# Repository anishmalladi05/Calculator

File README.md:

# Calculator
16 key calculator with a 128 by 32 pixel display and low profile choc switches. Uses circuit python. I made it to challenge myself and use a screen in my builds. I also wanted to try choc switches without building a whole keyboard.

## Assembly:
Look at the assembly video in the repo
<br></br>
Step 1:
<br></br>
Solder PCB components on
<br></br>
Step 2:
<br></br>
Assemble it into case according to the video

## Flashing:
To flash, press BOOT on the board, and while pressing boot, press reset, then release reset, and THEN release boot
<br></br>
Upload the UF2 File into the drive called RP1-RP2
<br></br>
Open the drive called CIRCUITPY
<br></br>
Delete everything in there
<br></br>
Replace it with everything in the folder called code so it looks like this:
<br></br>

<br></br>
Enjoy!

## Images:

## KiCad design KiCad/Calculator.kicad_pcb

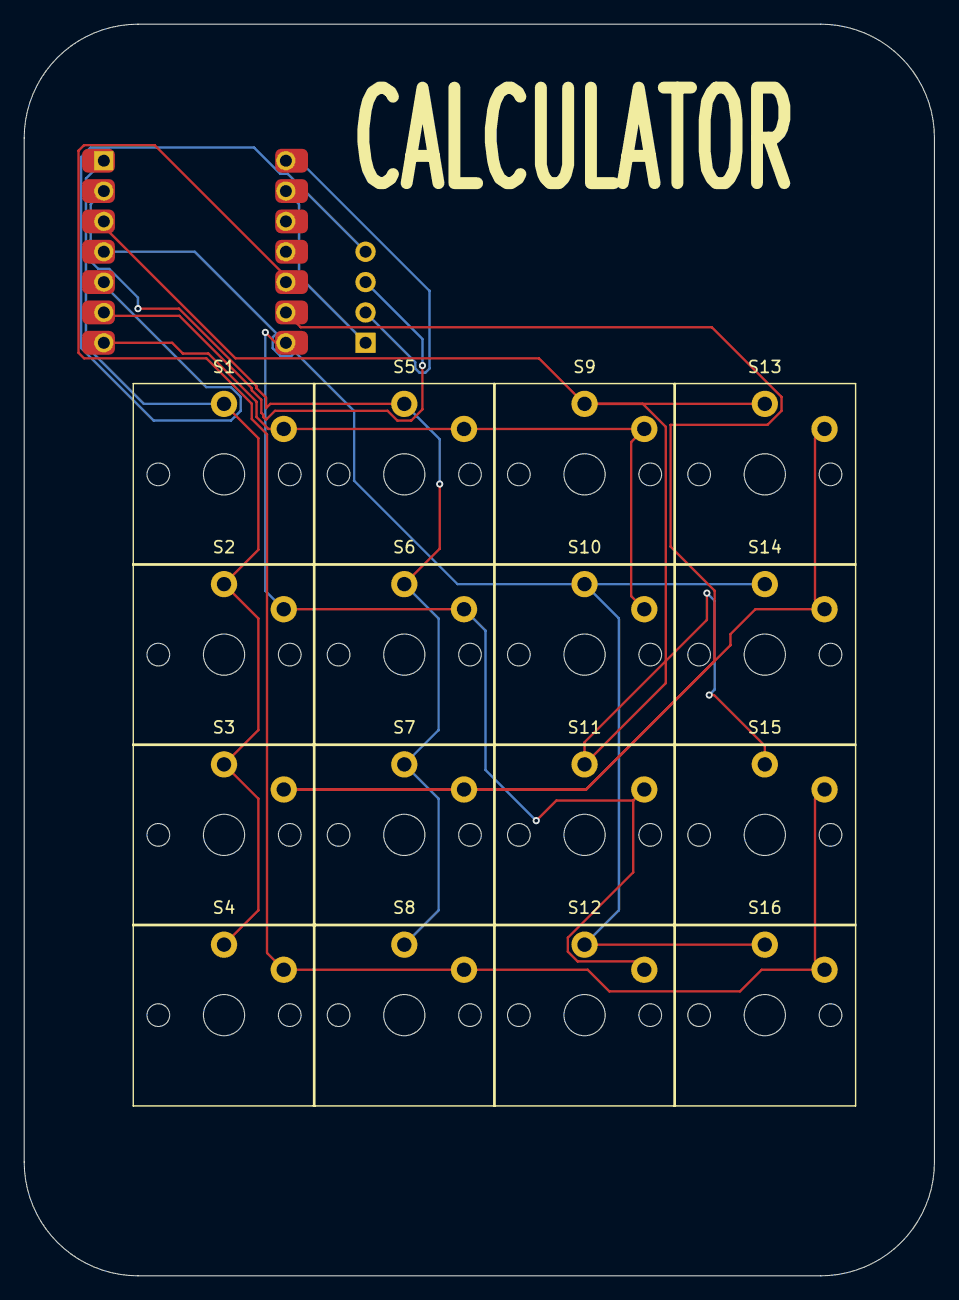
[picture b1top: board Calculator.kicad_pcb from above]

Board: 2 copper layers, 76.2 x 104.8 mm, 18 parts (0 on the bottom side), 12 nets.

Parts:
J1: OLED_128x32
S1, S2, S3, S4, S5, S6, S7, S8, S9, S10, S11, S12, S13, S14, S15, S16: Choc_V1_1.00u
U1: MCU_Seeed_XIAO_RP2040; Seeed_XIAO_RP2040

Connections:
1: S1.1, S2.1, S3.1, S4.1, U1.1 (PA02_A0_D0)
2: S5.1, S6.1, S7.1, S8.1, U1.2 (PA4_A1_D1)
3: S9.1, S11.1, S13.1, S15.1, U1.3 (PA10_A2_D2)
4: S10.1, S12.1, S14.1, S16.1, U1.4 (PA11_A3_D3)
5V: J1.2 (VCC), U1.14 (5V)
7: S1.2, S5.2, S9.2, S10.2, U1.7 (PB08_A6_D6_TX)
8: S2.2, S6.2, S11.2, S12.2, U1.8 (PB09_A7_D7_RX)
9: S3.2, S7.2, S13.2, S14.2, U1.9 (PA7_A8_D8_SCK)
10: S4.2, S8.2, S15.2, S16.2, U1.10 (PA5_A9_D9_MISO)
GND: J1.1 (GND), U1.13 (GND)
SCL: J1.3 (SCL), U1.6 (PA9_A5_D5_SCL)
SDA: J1.4 (SDA), U1.5 (PA8_A4_D4_SDA)
